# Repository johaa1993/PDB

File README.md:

# PDB

# Kill switch
The goal is to switch high current, voltage with logic level voltage and logic level current.
If somethings goes wrong then the user might want to kill the system until further damages happens.

Mechanical relay or MOSFET can be used for such application.

## MOSFET driver
The MOSFET can be damaged if driven incorectly.

### Drain-source resistance `R_ds`
Applying gate-source voltage will decrease drain-source resistance over time.
If the drain-source resistance decreases too slow while drain-source current is conducted then the MOSFET will heat up and possably get damaged.
The time it takes to reach fully turned on MOSFET depends on gate capacitance, 
gate resistance and the MOSFET gate driver ability to deliver current.

### Gate-source voltage `V_GS`
Applying too high gate-source voltage will damage the MOSFET.

### Parasitic oscillation
The MOSFET internal capacitance and the wires inductance combined will inevitably create a RLC curcuit.
A step response on the `V_GS` will have a oscilation. Higher gate resistance => higher damping, higher switch time. Lower gate resistance => lower damping, lower switch time.
It's up to the user to find a fine balance between the switch time and parasitic oscillation.

http://toshiba.semicon-storage.com/us/design-support/document/application-note.html
Application Precautions: Power MOSFET Application Notes

### More
Taking all these into consideration when designing a MOSFET driver is a hard task.

# Current sensor
The goal is to measure the both high current, low current.

# Fuse
The goal is too protect from short curcuit.

# Power status
The goal is to check if there power on the line.

# Battery cell monitor
The goal is to check if the battery cell is to low.

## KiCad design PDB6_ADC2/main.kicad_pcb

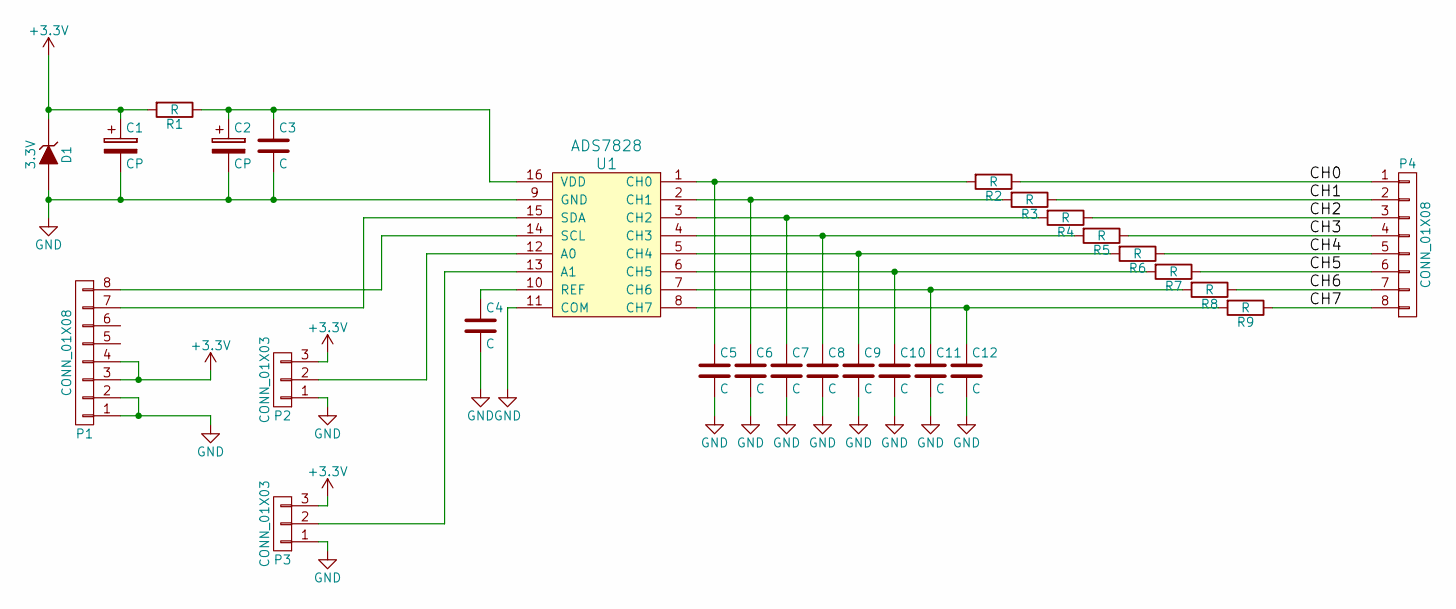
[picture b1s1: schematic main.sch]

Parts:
C1, C2: CP; SMD-1206_Pol
C3, C4, C5, C6, C7, C8, C9, C10, C11, C12: C; C_0805
D1: 3.3V; SOD-123
P1, P4: CONN_01X08; Pin_Header_Straight_1x08_Pitch2.00mm
P2, P3: CONN_01X03; Pad_3
R1, R2, R3, R4, R5, R6, R7, R8, R9: R; R_0805
U1: ADS7828; TSSOP-16_4.4x5mm_Pitch0.65mm

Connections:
+3V3: C1.1, D1.1 (K), P1.3, P1.4, P2.3, P3.3, R1.2
/CH0: P4.1, R2.1
/CH1: P4.2, R3.1
/CH2: P4.3, R4.1
/CH3: P4.4, R5.1
/CH4: P4.5, R6.1
/CH5: P4.6, R7.1
/CH6: P4.7, R8.1
/CH7: P4.8, R9.1
GND: C1.2, C2.2, C3.2, C4.2, C5.2, C6.2, C7.2, C8.2, C9.2, C10.2, C11.2, C12.2, D1.2 (A), P1.1, P1.2, P2.1, P3.1, U1.9 (GND), U1.11 (COM)
unnamed: C2.1, C3.1, R1.1, U1.16 (VDD)
unnamed: C4.1, U1.10 (REF)
unnamed: C5.1, R2.2, U1.1 (CH0)
unnamed: C6.1, R3.2, U1.2 (CH1)
unnamed: C7.1, R4.2, U1.3 (CH2)
unnamed: C8.1, R5.2, U1.4 (CH3)
unnamed: C9.1, R6.2, U1.5 (CH4)
unnamed: C10.1, R7.2, U1.6 (CH5)
unnamed: C11.1, R8.2, U1.7 (CH6)
unnamed: C12.1, R9.2, U1.8 (CH7)
unnamed: P1.7, U1.15 (SDA)
unnamed: P1.8, U1.14 (SCL)
unnamed: P2.2, U1.12 (A0)
unnamed: P3.2, U1.13 (A1)

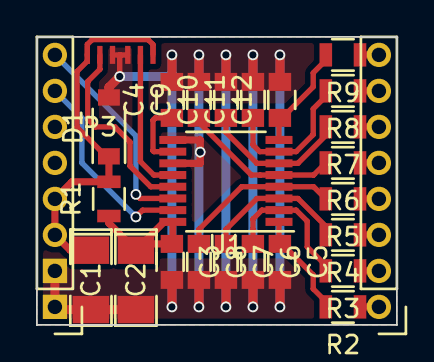
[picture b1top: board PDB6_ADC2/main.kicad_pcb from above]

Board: 2 copper layers, 20.0 x 16.0 mm, 27 parts (0 on the bottom side), 24 nets.

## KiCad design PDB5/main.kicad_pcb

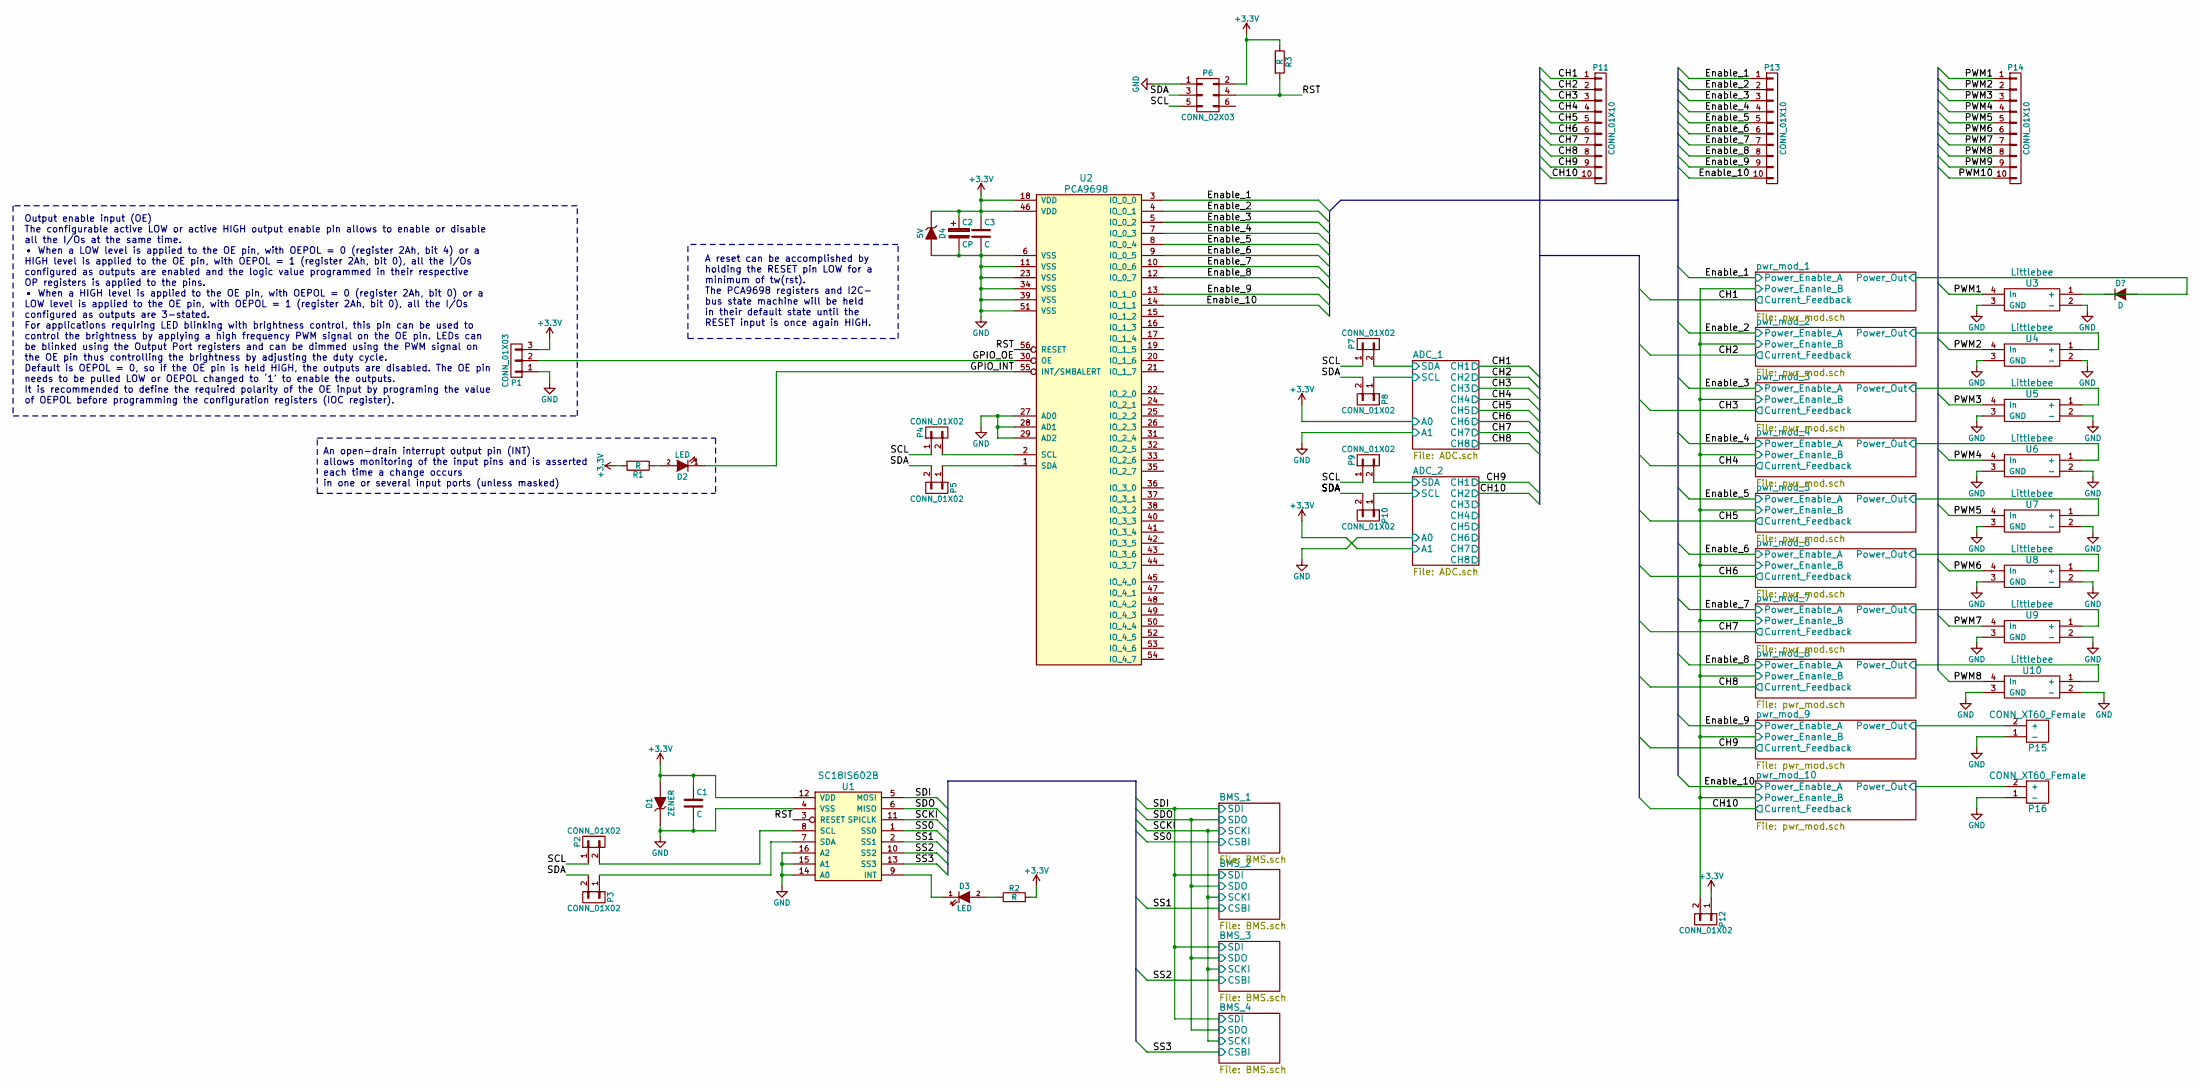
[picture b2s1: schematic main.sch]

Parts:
C1, C3: C; C_0805
C2: CP; SMD-2010_Pol
D1: ZENER; SOD-123
D2, D3: LED; LED_0603
D4: 5V; SOD-123
P1: CONN_01X03; Pin_Header_Straight_1x03
P2, P3, P4, P5, P7, P8, P9, P10, P12: CONN_01X02; Pin_Header_Straight_1x02
P6: CONN_02X03; Pin_Header_Straight_2x03
P11, P13, P14: CONN_01X10; Pin_Header_Straight_1x10
P15, P16: CONN_XT60_Female; XT60
R1, R2: R; R_0603
R3: R
U1: SC18IS602B; TSSOP-16_4.4x5mm_Pitch0.65mm
U2: PCA9698; TSSOP-56_6.1x14mm_Pitch0.5mm
U3, U4, U5, U6, U7, U8, U9, U10: Littlebee

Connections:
+3V3: C1.1, C2.1, C3.1, D1.2 (A), D4.1 (K), P1.3, P6.2, P12.1, R1.2, R2.2, R3.1, U1.12 (VDD), U2.18 (VDD), U2.46 (VDD); also elsewhere on the board
/ADC_1/SCL: P8.1; also elsewhere on the board
/ADC_1/SDA: P7.2; also elsewhere on the board
/ADC_2/SCL: P10.1; also elsewhere on the board
/ADC_2/SDA: P9.2; also elsewhere on the board
/CH1: P11.1; also elsewhere on the board
/CH2: P11.2; also elsewhere on the board
/CH3: P11.3; also elsewhere on the board
/CH4: P11.4; also elsewhere on the board
/CH5: P11.5; also elsewhere on the board
/CH6: P11.6; also elsewhere on the board
/CH7: P11.7; also elsewhere on the board
/CH8: P11.8; also elsewhere on the board
/CH9: P11.9; also elsewhere on the board
/CH10: P11.10; also elsewhere on the board
/Enable_1: P13.1, U2.3 (IO_0_0); also elsewhere on the board
/Enable_2: P13.2, U2.4 (IO_0_1); also elsewhere on the board
/Enable_3: P13.3, U2.5 (IO_0_2); also elsewhere on the board
/Enable_4: P13.4, U2.7 (IO_0_3); also elsewhere on the board
/Enable_5: P13.5, U2.8 (IO_0_4); also elsewhere on the board
/Enable_6: P13.6, U2.9 (IO_0_5); also elsewhere on the board
/Enable_7: P13.7, U2.10 (IO_0_6); also elsewhere on the board
/Enable_8: P13.8, U2.12 (IO_0_7); also elsewhere on the board
/Enable_9: P13.9, U2.13 (IO_1_0); also elsewhere on the board
/Enable_10: P13.10, U2.14 (IO_1_1); also elsewhere on the board
/GPIO_INT: D2.1 (K), U2.55 (INT/SMBALERT)
/GPIO_OE: P1.2, U2.30 (OE)
/PWM1: P14.1, U3.4 (In)
/PWM2: P14.2, U4.4 (In)
/PWM3: P14.3, U5.4 (In)
/PWM4: P14.4, U6.4 (In)
/PWM5: P14.5, U7.4 (In)
/PWM6: P14.6, U8.4 (In)
/PWM7: P14.7, U9.4 (In)
/PWM8: P14.8, U10.4 (In)
/RST: P6.4, R3.2, U1.3 (RESET), U2.56 (RESET)
/SCKI: U1.11 (SPICLK); also elsewhere on the board
/SCL: P2.1, P4.1, P6.5, P7.1, P9.1
/SDA: P3.2, P5.2, P6.3, P8.2, P10.2
/SDI: U1.5 (MOSI); also elsewhere on the board
/SDO: U1.6 (MISO); also elsewhere on the board
/SS0: U1.1 (SS0); also elsewhere on the board
/SS1: U1.2 (SS1); also elsewhere on the board
/SS2: U1.10 (SS2); also elsewhere on the board
/SS3: U1.13 (SS3); also elsewhere on the board
/pwr_mod_1/Power_Enanle_B: P12.2; also elsewhere on the board
/pwr_mod_1/Power_Out: U3.1 (+); also elsewhere on the board
/pwr_mod_2/Power_Out: U4.1 (+); also elsewhere on the board
/pwr_mod_3/Power_Out: U5.1 (+); also elsewhere on the board
/pwr_mod_4/Power_Out: U6.1 (+); also elsewhere on the board
/pwr_mod_5/Power_Out: U7.1 (+); also elsewhere on the board
/pwr_mod_6/Power_Out: U8.1 (+); also elsewhere on the board
/pwr_mod_7/Power_Out: U9.1 (+); also elsewhere on the board
/pwr_mod_8/Power_Out: U10.1 (+); also elsewhere on the board
/pwr_mod_9/Power_Out: P15.2 (+); also elsewhere on the board
/pwr_mod_10/Power_Out: P16.2 (+); also elsewhere on the board
GND: C1.2, C2.2, C3.2, D1.1 (K), D4.2 (A), P1.1, P6.1, P15.1 (-), P16.1 (-), U1.4 (VSS), U1.14 (A0), U1.15 (A1), U1.16 (A2), U2.6 (VSS), U2.11 (VSS), U2.23 (VSS), U2.27 (AD0), U2.28 (AD1), U2.29 (AD2), U2.34 (VSS), U2.39 (VSS), U2.51 (VSS), U3.2 (-), U3.3 (GND), U4.2 (-), U4.3 (GND), U5.2 (-), U5.3 (GND), U6.2 (-), U6.3 (GND), U7.2 (-), U7.3 (GND), U8.2 (-), U8.3 (GND), U9.2 (-), U9.3 (GND), U10.2 (-), U10.3 (GND); also elsewhere on the board
unnamed: D2.2 (A), R1.1
unnamed: D3.1 (K), U1.9 (INT)
unnamed: D3.2 (A), R2.1
unnamed: P2.2, U1.8 (SCL)
unnamed: P3.1, U1.7 (SDA)
unnamed: P4.2, U2.2 (SCL)
unnamed: P5.1, U2.1 (SDA)

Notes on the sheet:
An open-drain interrupt output pin (INT) allows monitoring of the input pins and is asserted each time a change occurs in one or several input ports (unless masked)
Output enable input (OE) The configurable active LOW or active HIGH output enable pin allows to enable or disable all the I/Os at the same time. • When a LOW level is applied to the OE pin, with OEPOL = 0 (register 2Ah, bit 4) or a HIGH level is applied to the OE pin, with OEPOL = 1 (register 2Ah, 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
A reset can be accomplished by holding the RESET pin LOW for a minimum of tw(rst). The PCA9698 registers and I2C- bus state machine will be held in their default state until the RESET input is once again HIGH.

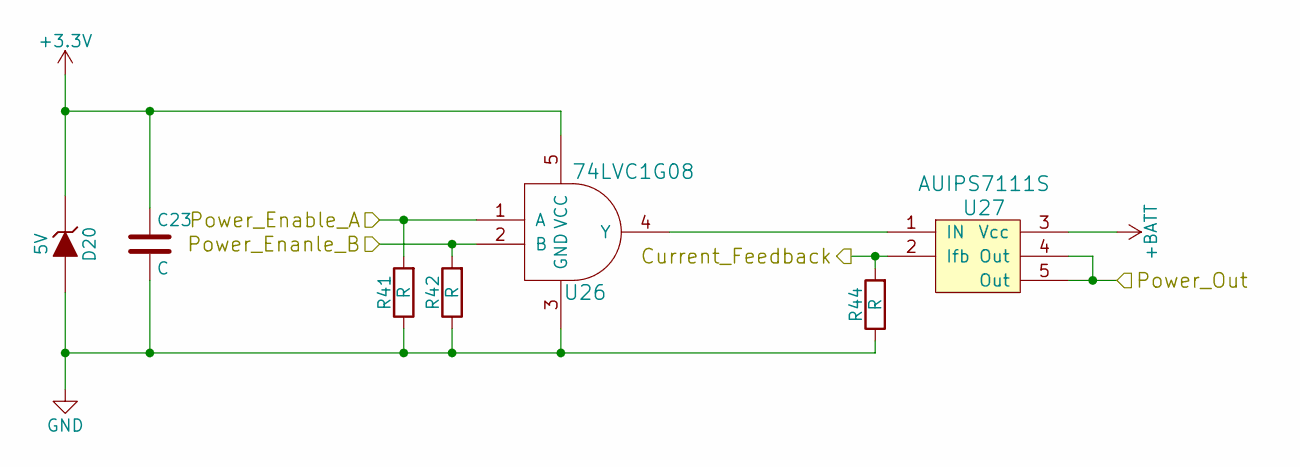
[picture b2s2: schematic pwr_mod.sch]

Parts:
C4: C; C_0805
D5: 5V; SOD-123
R4, R7, R26: R; R_0603
U11: 74LVC1G08; SOT-353
U12: AUIPS7111S; TO-263-!3

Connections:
+3V3: C4.1, D5.1 (K), U11.5 (VCC); also elsewhere on the board
+BATT: U12.3 (Vcc); also elsewhere on the board
/CH1: R7.2, U12.2 (Ifb); also elsewhere on the board
/Enable_1: R4.2, U11.1 (A); also elsewhere on the board
/pwr_mod_1/Power_Enanle_B: R26.2, U11.2 (B); also elsewhere on the board
/pwr_mod_1/Power_Out: U12.4 (Out), U12.5 (Out); also elsewhere on the board
GND: C4.2, D5.2 (A), R4.1, R7.1, R26.1, U11.3 (GND); also elsewhere on the board
unnamed: U11.4 (Y), U12.1 (IN)

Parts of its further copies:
C5, C18, C19, C20, C21, C22, C23, C24, C25: C; C_0805
D7, D10, D12, D14, D16, D18, D20, D22, D24: 5V; SOD-123
R5, R8, R9, R11, R21, R22, R24, R25, R28, R29, R30, R32, R33, R34, R36, R37, R38, R40, R41, R42, R44, R45, R46, R48, R49, R50, R52: R; R_0603
U13, U16, U18, U20, U22, U24, U26, U28, U30: 74LVC1G08; SOT-353
U14, U17, U19, U21, U23, U25, U27, U29, U31: AUIPS7111S; TO-263-!3

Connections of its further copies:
+3V3: C5.1, C18.1, C19.1, C20.1, C21.1, C22.1, C23.1, C24.1, C25.1, D7.1 (K), D10.1 (K), D12.1 (K), D14.1 (K), D16.1 (K), D18.1 (K), D20.1 (K), D22.1 (K), D24.1 (K), U13.5 (VCC), U16.5 (VCC), U18.5 (VCC), U20.5 (VCC), U22.5 (VCC), U24.5 (VCC), U26.5 (VCC), U28.5 (VCC), U30.5 (VCC); also elsewhere on the board
+BATT: U14.3 (Vcc), U17.3 (Vcc), U19.3 (Vcc), U21.3 (Vcc), U23.3 (Vcc), U25.3 (Vcc), U27.3 (Vcc), U29.3 (Vcc), U31.3 (Vcc); also elsewhere on the board
/CH2: R11.2, U14.2 (Ifb); also elsewhere on the board
/CH3: R24.2, U17.2 (Ifb); also elsewhere on the board
/CH4: R28.2, U19.2 (Ifb); also elsewhere on the board
/CH5: R32.2, U21.2 (Ifb); also elsewhere on the board
/CH6: R36.2, U23.2 (Ifb); also elsewhere on the board
/CH7: R40.2, U25.2 (Ifb); also elsewhere on the board
/CH8: R44.2, U27.2 (Ifb); also elsewhere on the board
/CH9: R48.2, U29.2 (Ifb); also elsewhere on the board
/CH10: R52.2, U31.2 (Ifb); also elsewhere on the board
/Enable_2: R8.2, U13.1 (A); also elsewhere on the board
/Enable_3: R21.2, U16.1 (A); also elsewhere on the board
/Enable_4: R25.2, U18.1 (A); also elsewhere on the board
/Enable_5: R29.2, U20.1 (A); also elsewhere on the board
/Enable_6: R33.2, U22.1 (A); also elsewhere on the board
/Enable_7: R37.2, U24.1 (A); also elsewhere on the board
/Enable_8: R41.2, U26.1 (A); also elsewhere on the board
/Enable_9: R45.2, U28.1 (A); also elsewhere on the board
/Enable_10: R49.2, U30.1 (A); also elsewhere on the board
/pwr_mod_1/Power_Enanle_B: R5.2, R9.2, R22.2, R30.2, R34.2, R38.2, R42.2, R46.2, R50.2, U13.2 (B), U16.2 (B), U18.2 (B), U20.2 (B), U22.2 (B), U24.2 (B), U26.2 (B), U28.2 (B), U30.2 (B); also elsewhere on the board
/pwr_mod_2/Power_Out: U14.4 (Out), U14.5 (Out); also elsewhere on the board
/pwr_mod_3/Power_Out: U17.4 (Out), U17.5 (Out); also elsewhere on the board
/pwr_mod_4/Power_Out: U19.4 (Out), U19.5 (Out); also elsewhere on the board
/pwr_mod_5/Power_Out: U21.4 (Out), U21.5 (Out); also elsewhere on the board
/pwr_mod_6/Power_Out: U23.4 (Out), U23.5 (Out); also elsewhere on the board
/pwr_mod_7/Power_Out: U25.4 (Out), U25.5 (Out); also elsewhere on the board
/pwr_mod_8/Power_Out: U27.4 (Out), U27.5 (Out); also elsewhere on the board
/pwr_mod_9/Power_Out: U29.4 (Out), U29.5 (Out); also elsewhere on the board
/pwr_mod_10/Power_Out: U31.4 (Out), U31.5 (Out); also elsewhere on the board
GND: C5.2, C18.2, C19.2, C20.2, C21.2, C22.2, C23.2, C24.2, C25.2, D7.2 (A), D10.2 (A), D12.2 (A), D14.2 (A), D16.2 (A), D18.2 (A), D20.2 (A), D22.2 (A), D24.2 (A), R5.1, R8.1, R9.1, R11.1, R21.1, R22.1, R24.1, R25.1, R28.1, R29.1, R30.1, R32.1, R33.1, R34.1, R36.1, R37.1, R38.1, R40.1, R41.1, R42.1, R44.1, R45.1, R46.1, R48.1, R49.1, R50.1, R52.1, U13.3 (GND), U16.3 (GND), U18.3 (GND), U20.3 (GND), U22.3 (GND), U24.3 (GND), U26.3 (GND), U28.3 (GND), U30.3 (GND); also elsewhere on the board
unnamed: U13.4 (Y), U14.1 (IN)
unnamed: U16.4 (Y), U17.1 (IN)
unnamed: U18.4 (Y), U19.1 (IN)
unnamed: U20.4 (Y), U21.1 (IN)
unnamed: U22.4 (Y), U23.1 (IN)
unnamed: U24.4 (Y), U25.1 (IN)
unnamed: U26.4 (Y), U27.1 (IN)
unnamed: U28.4 (Y), U29.1 (IN)
unnamed: U30.4 (Y), U31.1 (IN)

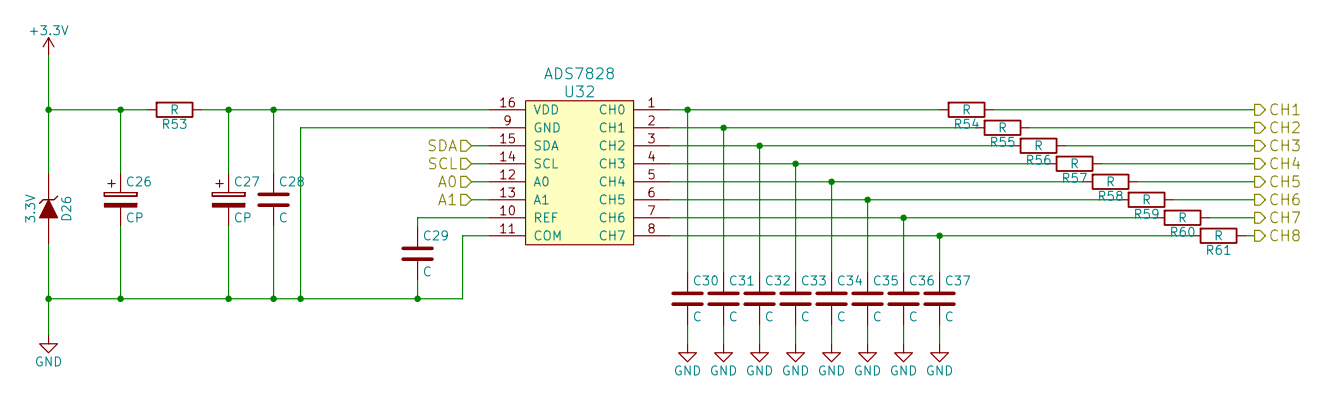
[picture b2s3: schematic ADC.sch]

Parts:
C6, C7: CP; SMD-2010_Pol
C8, C9, C10, C11, C12, C13, C14, C15, C16, C17: C; C_0805
D9: 3.3V; SOD-123
R12, R13, R14, R15, R16, R17, R18, R19, R20: R; R_0603
U15: ADS7828; TSSOP-16_4.4x5mm_Pitch0.65mm

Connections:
+3V3: C6.1, D9.1 (K), R12.2, U15.12 (A0); also elsewhere on the board
/ADC_1/SCL: U15.14 (SCL); also elsewhere on the board
/ADC_1/SDA: U15.15 (SDA); also elsewhere on the board
/CH1: R13.1; also elsewhere on the board
/CH2: R14.1; also elsewhere on the board
/CH3: R15.1; also elsewhere on the board
/CH4: R16.1; also elsewhere on the board
/CH5: R17.1; also elsewhere on the board
/CH6: R18.1; also elsewhere on the board
/CH7: R19.1; also elsewhere on the board
/CH8: R20.1; also elsewhere on the board
GND: C6.2, C7.2, C8.2, C9.2, C10.2, C11.2, C12.2, C13.2, C14.2, C15.2, C16.2, C17.2, D9.2 (A), U15.9 (GND), U15.11 (COM), U15.13 (A1); also elsewhere on the board
unnamed: C7.1, C8.1, R12.1, U15.16 (VDD)
unnamed: C9.1, U15.10 (REF)
unnamed: C10.1, R13.2, U15.1 (CH0)
unnamed: C11.1, R14.2, U15.2 (CH1)
unnamed: C12.1, R15.2, U15.3 (CH2)
unnamed: C13.1, R16.2, U15.4 (CH3)
unnamed: C14.1, R17.2, U15.5 (CH4)
unnamed: C15.1, R18.2, U15.6 (CH5)
unnamed: C16.1, R19.2, U15.7 (CH6)
unnamed: C17.1, R20.2, U15.8 (CH7)

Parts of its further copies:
C26, C27: CP; SMD-2010_Pol
C28, C29, C30, C31, C32, C33, C34, C35, C36, C37: C; C_0805
D26: 3.3V; SOD-123
R53, R54, R55, R56, R57, R58, R59, R60, R61: R; R_0603
U32: ADS7828; TSSOP-16_4.4x5mm_Pitch0.65mm

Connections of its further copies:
+3V3: C26.1, D26.1 (K), R53.2, U32.13 (A1); also elsewhere on the board
/ADC_2/SCL: U32.14 (SCL); also elsewhere on the board
/ADC_2/SDA: U32.15 (SDA); also elsewhere on the board
/CH9: R54.1; also elsewhere on the board
/CH10: R55.1; also elsewhere on the board
GND: C26.2, C27.2, C28.2, C29.2, C30.2, C31.2, C32.2, C33.2, C34.2, C35.2, C36.2, C37.2, D26.2 (A), U32.9 (GND), U32.11 (COM), U32.12 (A0); also elsewhere on the board
unnamed: C27.1, C28.1, R53.1, U32.16 (VDD)
unnamed: C29.1, U32.10 (REF)
unnamed: C30.1, R54.2, U32.1 (CH0)
unnamed: C31.1, R55.2, U32.2 (CH1)
unnamed: C32.1, R56.2, U32.3 (CH2)
unnamed: C33.1, R57.2, U32.4 (CH3)
unnamed: C34.1, R58.2, U32.5 (CH4)
unnamed: C35.1, R59.2, U32.6 (CH5)
unnamed: C36.1, R60.2, U32.7 (CH6)
unnamed: C37.1, R61.2, U32.8 (CH7)

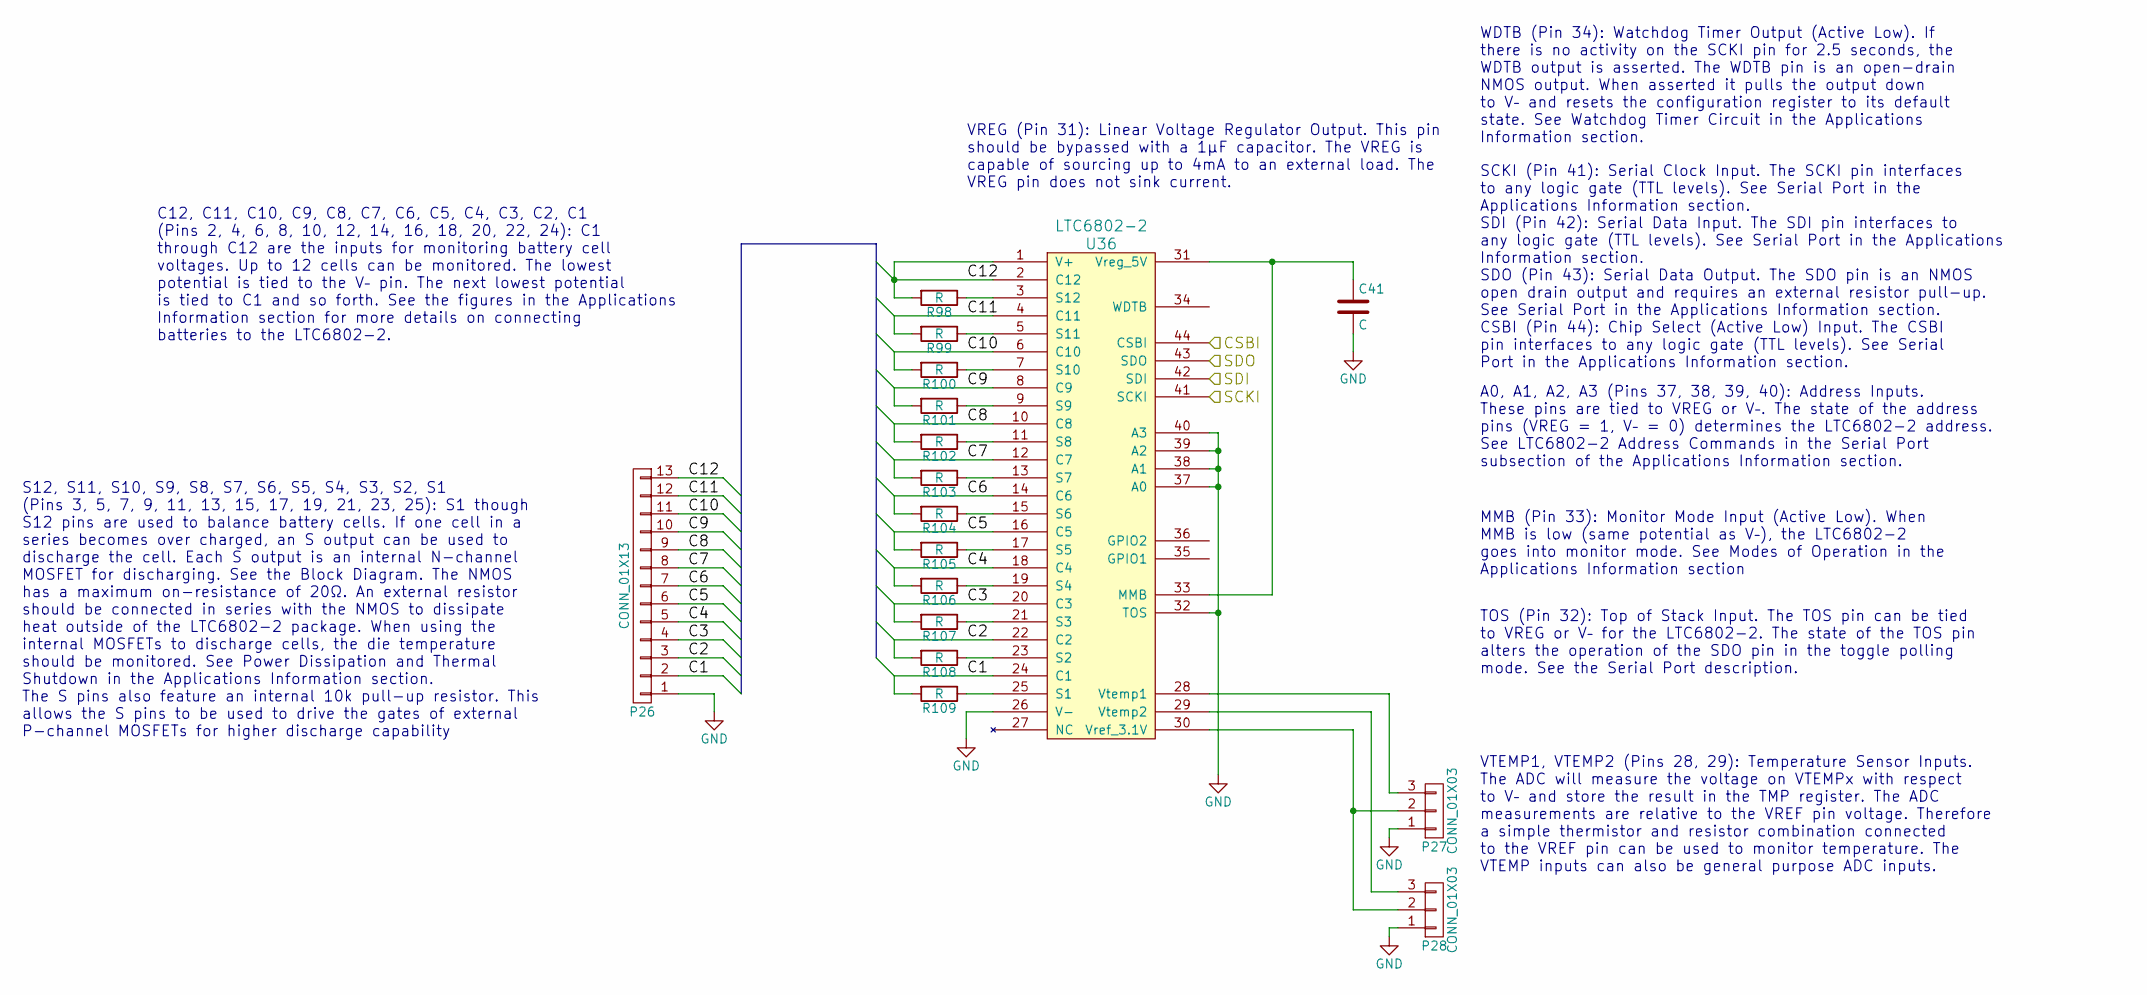
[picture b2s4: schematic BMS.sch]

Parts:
C38: C; C_0805
P17: CONN_01X13; Pin_Header_Straight_1x13
P18, P19: CONN_01X03; Pin_Header_Straight_1x03
R62, R63, R64, R65, R66, R67, R68, R69, R70, R71, R72, R73: R; R_0805
U33: LTC6802-2; SSOP-44

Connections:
/BMS_1/C1: P17.2, R73.2, U33.24 (C1)
/BMS_1/C2: P17.3, R72.2, U33.22 (C2)
/BMS_1/C3: P17.4, R71.2, U33.20 (C3)
/BMS_1/C4: P17.5, R70.2, U33.18 (C4)
/BMS_1/C5: P17.6, R69.2, U33.16 (C5)
/BMS_1/C6: P17.7, R68.2, U33.14 (C6)
/BMS_1/C7: P17.8, R67.2, U33.12 (C7)
/BMS_1/C8: P17.9, R66.2, U33.10 (C8)
/BMS_1/C9: P17.10, R65.2, U33.8 (C9)
/BMS_1/C10: P17.11, R64.2, U33.6 (C10)
/BMS_1/C11: P17.12, R63.2, U33.4 (C11)
/BMS_1/C12: P17.13, R62.2, U33.1 (V+), U33.2 (C12)
/SCKI: U33.41 (SCKI); also elsewhere on the board
/SDI: U33.42 (SDI); also elsewhere on the board
/SDO: U33.43 (SDO); also elsewhere on the board
/SS0: U33.44 (CSBI); also elsewhere on the board
GND: C38.2, P17.1, P18.1, P19.1, U33.26 (V-), U33.32 (TOS), U33.37 (A0), U33.38 (A1), U33.39 (A2), U33.40 (A3); also elsewhere on the board
unnamed: C38.1, U33.31 (Vreg_5V), U33.33 (MMB)
unnamed: P18.2, P19.2, U33.30 (Vref_3.1V)
unnamed: P18.3, U33.28 (Vtemp1)
unnamed: P19.3, U33.29 (Vtemp2)
unnamed: R62.1, U33.3 (S12)
unnamed: R63.1, U33.5 (S11)
unnamed: R64.1, U33.7 (S10)
unnamed: R65.1, U33.9 (S9)
unnamed: R66.1, U33.11 (S8)
unnamed: R67.1, U33.13 (S7)
unnamed: R68.1, U33.15 (S6)
unnamed: R69.1, U33.17 (S5)
unnamed: R70.1, U33.19 (S4)
unnamed: R71.1, U33.21 (S3)
unnamed: R72.1, U33.23 (S2)
unnamed: R73.1, U33.25 (S1)

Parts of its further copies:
C39, C40, C41: C; C_0805
P20, P23, P26: CONN_01X13; Pin_Header_Straight_1x13
P21, P22, P24, P25, P27, P28: CONN_01X03; Pin_Header_Straight_1x03
R74, R75, R76, R77, R78, R79, R80, R81, R82, R83, R84, R85, R86, R87, R88, R89, R90, R91, R92, R93, R94, R95, R96, R97, R98, R99, R100, R101, R102, R103, R104, R105, R106, R107, R108, R109: R; R_0805
U34, U35, U36: LTC6802-2; SSOP-44

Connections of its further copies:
/BMS_2/C1: P20.2, R85.2, U34.24 (C1)
/BMS_2/C2: P20.3, R84.2, U34.22 (C2)
/BMS_2/C3: P20.4, R83.2, U34.20 (C3)
/BMS_2/C4: P20.5, R82.2, U34.18 (C4)
/BMS_2/C5: P20.6, R81.2, U34.16 (C5)
/BMS_2/C6: P20.7, R80.2, U34.14 (C6)
/BMS_2/C7: P20.8, R79.2, U34.12 (C7)
/BMS_2/C8: P20.9, R78.2, U34.10 (C8)
/BMS_2/C9: P20.10, R77.2, U34.8 (C9)
/BMS_2/C10: P20.11, R76.2, U34.6 (C10)
/BMS_2/C11: P20.12, R75.2, U34.4 (C11)
/BMS_2/C12: P20.13, R74.2, U34.1 (V+), U34.2 (C12)
/BMS_3/C1: P23.2, R97.2, U35.24 (C1)
/BMS_3/C2: P23.3, R96.2, U35.22 (C2)
/BMS_3/C3: P23.4, R95.2, U35.20 (C3)
/BMS_3/C4: P23.5, R94.2, U35.18 (C4)
/BMS_3/C5: P23.6, R93.2, U35.16 (C5)
/BMS_3/C6: P23.7, R92.2, U35.14 (C6)
/BMS_3/C7: P23.8, R91.2, U35.12 (C7)
/BMS_3/C8: P23.9, R90.2, U35.10 (C8)
/BMS_3/C9: P23.10, R89.2, U35.8 (C9)
/BMS_3/C10: P23.11, R88.2, U35.6 (C10)
/BMS_3/C11: P23.12, R87.2, U35.4 (C11)
/BMS_3/C12: P23.13, R86.2, U35.1 (V+), U35.2 (C12)
/BMS_4/C1: P26.2, R109.2, U36.24 (C1)
/BMS_4/C2: P26.3, R108.2, U36.22 (C2)
/BMS_4/C3: P26.4, R107.2, U36.20 (C3)
/BMS_4/C4: P26.5, R106.2, U36.18 (C4)
/BMS_4/C5: P26.6, R105.2, U36.16 (C5)
/BMS_4/C6: P26.7, R104.2, U36.14 (C6)
/BMS_4/C7: P26.8, R103.2, U36.12 (C7)
/BMS_4/C8: P26.9, R102.2, U36.10 (C8)
/BMS_4/C9: P26.10, R101.2, U36.8 (C9)
/BMS_4/C10: P26.11, R100.2, U36.6 (C10)
/BMS_4/C11: P26.12, R99.2, U36.4 (C11)
/BMS_4/C12: P26.13, R98.2, U36.1 (V+), U36.2 (C12)
/SCKI: U34.41 (SCKI), U35.41 (SCKI), U36.41 (SCKI); also elsewhere on the board
/SDI: U34.42 (SDI), U35.42 (SDI), U36.42 (SDI); also elsewhere on the board
/SDO: U34.43 (SDO), U35.43 (SDO), U36.43 (SDO); also elsewhere on the board
/SS1: U34.44 (CSBI); also elsewhere on the board
/SS2: U35.44 (CSBI); also elsewhere on the board
/SS3: U36.44 (CSBI); also elsewhere on the board
GND: C39.2, C40.2, C41.2, P20.1, P21.1, P22.1, P23.1, P24.1, P25.1, P26.1, P27.1, P28.1, U34.26 (V-), U34.32 (TOS), U34.37 (A0), U34.38 (A1), U34.39 (A2), U34.40 (A3), U35.26 (V-), U35.32 (TOS), U35.37 (A0), U35.38 (A1), U35.39 (A2), U35.40 (A3), U36.26 (V-), U36.32 (TOS), U36.37 (A0), U36.38 (A1), U36.39 (A2), U36.40 (A3); also elsewhere on the board
unnamed: C39.1, U34.31 (Vreg_5V), U34.33 (MMB)
unnamed: C40.1, U35.31 (Vreg_5V), U35.33 (MMB)
unnamed: C41.1, U36.31 (Vreg_5V), U36.33 (MMB)
unnamed: P21.2, P22.2, U34.30 (Vref_3.1V)
unnamed: P21.3, U34.28 (Vtemp1)
unnamed: P22.3, U34.29 (Vtemp2)
unnamed: P24.2, P25.2, U35.30 (Vref_3.1V)
unnamed: P24.3, U35.28 (Vtemp1)
unnamed: P25.3, U35.29 (Vtemp2)
unnamed: P27.2, P28.2, U36.30 (Vref_3.1V)
unnamed: P27.3, U36.28 (Vtemp1)
unnamed: P28.3, U36.29 (Vtemp2)
unnamed: R74.1, U34.3 (S12)
unnamed: R75.1, U34.5 (S11)
unnamed: R76.1, U34.7 (S10)
unnamed: R77.1, U34.9 (S9)
unnamed: R78.1, U34.11 (S8)
unnamed: R79.1, U34.13 (S7)
unnamed: R80.1, U34.15 (S6)
unnamed: R81.1, U34.17 (S5)
unnamed: R82.1, U34.19 (S4)
unnamed: R83.1, U34.21 (S3)
unnamed: R84.1, U34.23 (S2)
unnamed: R85.1, U34.25 (S1)
unnamed: R86.1, U35.3 (S12)
unnamed: R87.1, U35.5 (S11)
unnamed: R88.1, U35.7 (S10)
unnamed: R89.1, U35.9 (S9)
unnamed: R90.1, U35.11 (S8)
unnamed: R91.1, U35.13 (S7)
unnamed: R92.1, U35.15 (S6)
unnamed: R93.1, U35.17 (S5)
unnamed: R94.1, U35.19 (S4)
unnamed: R95.1, U35.21 (S3)
unnamed: R96.1, U35.23 (S2)
unnamed: R97.1, U35.25 (S1)
unnamed: R98.1, U36.3 (S12)
unnamed: R99.1, U36.5 (S11)
unnamed: R100.1, U36.7 (S10)
unnamed: R101.1, U36.9 (S9)
unnamed: R102.1, U36.11 (S8)
unnamed: R103.1, U36.13 (S7)
unnamed: R104.1, U36.15 (S6)
unnamed: R105.1, U36.17 (S5)
unnamed: R106.1, U36.19 (S4)
unnamed: R107.1, U36.21 (S3)
unnamed: R108.1, U36.23 (S2)
unnamed: R109.1, U36.25 (S1)

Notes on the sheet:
WDTB (Pin 34): Watchdog Timer Output (Active Low). If there is no activity on the SCKI pin for 2.5 seconds, the WDTB output is asserted. The WDTB pin is an open-drain NMOS output. When asserted it pulls the output down to V– and resets the configuration register to its default state. See Watchdog T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
VTEMP1, VTEMP2 (Pins 28, 29): Temperature Sensor Inputs. The ADC will measure the voltage on VTEMPx with respect to V– and store the result in the TMP register. The ADC measurements are relative to the VREF pin voltage. Therefore a simple thermistor and resistor combination connected to the VREF pi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
SCKI (Pin 41): Serial Clock Input. The SCKI pin interfaces to any logic gate (TTL levels). See Serial Port in the Applications Information section. SDI (Pin 42): Serial Data Input. The SDI pin interfaces to any logic gate (TTL levels). See Serial Port in the Applications Information section. SDO (P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
C12, C11, C10, C9, C8, C7, C6, C5, C4, C3, C2, C1 (Pins 2, 4, 6, 8, 10, 12, 14, 16, 18, 20, 22, 24): C1 through C12 are the inputs for monitoring battery cell voltages. Up to 12 cells can be monitored. The lowest potential is tied to the V– pin. The next lowest potential is tied to C1 and so forth.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
S12, S11, S10, S9, S8, S7, S6, S5, S4, S3, S2, S1 (Pins 3, 5, 7, 9, 11, 13, 15, 17, 19, 21, 23, 25): S1 though S12 pins are used to balance battery cells. If one cell in a series becomes over charged, an S output can be used to discharge the cell. Each S output is an internal N-channel MOSFET for d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
MMB (Pin 33): Monitor Mode Input (Active Low). When MMB is low (same potential as V–), the LTC6802-2 goes into monitor mode. See Modes of Operation in the Applications Information section
TOS (Pin 32): Top of Stack Input. The TOS pin can be tied to VREG or V– for the LTC6802-2. The state of the TOS pin alters the operation of the SDO pin in the toggle polling mode. See the Serial Port description.
A0, A1, A2, A3 (Pins 37, 38, 39, 40): Address Inputs. These pins are tied to VREG or V–. The state of the address pins (VREG = 1, V– = 0) determines the LTC6802-2 address. See LTC6802-2 Address Commands in the Serial Port subsection of the Applications Information section.
VREG (Pin 31): Linear Voltage Regulator Output. This pin should be bypassed with a 1µF capacitor. The VREG is capable of sourcing up to 4mA to an external load. The VREG pin does not sink current.

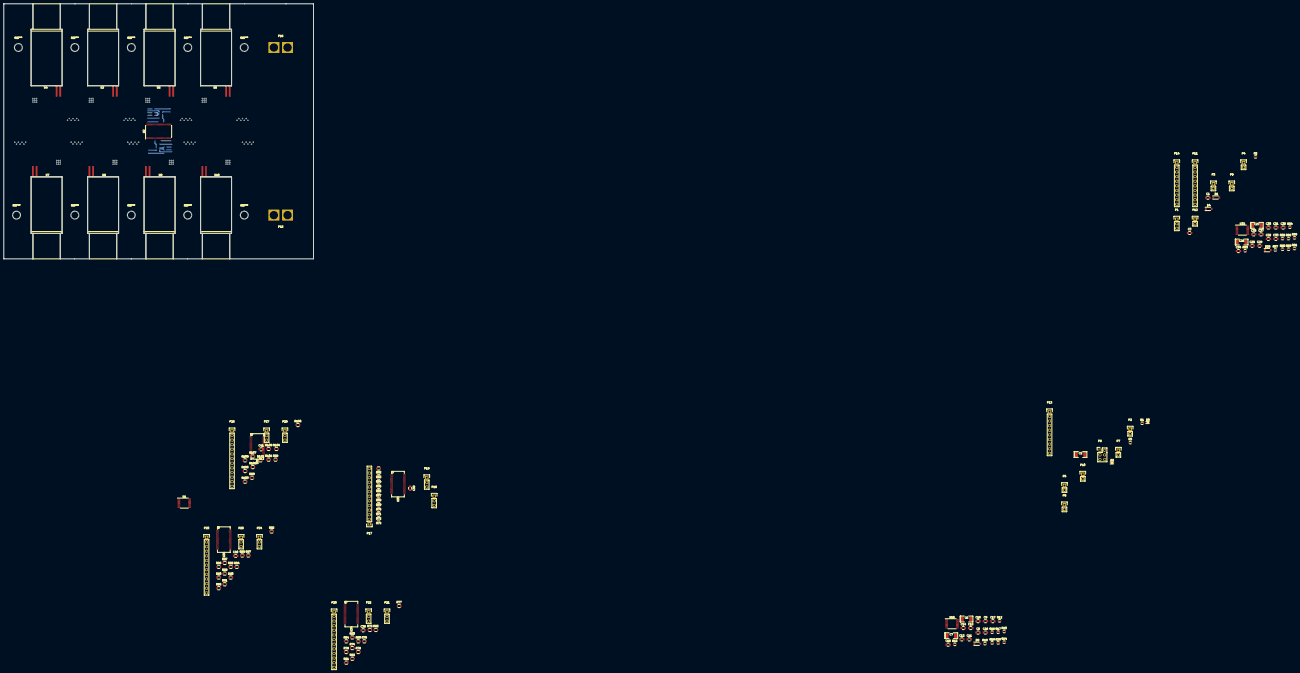
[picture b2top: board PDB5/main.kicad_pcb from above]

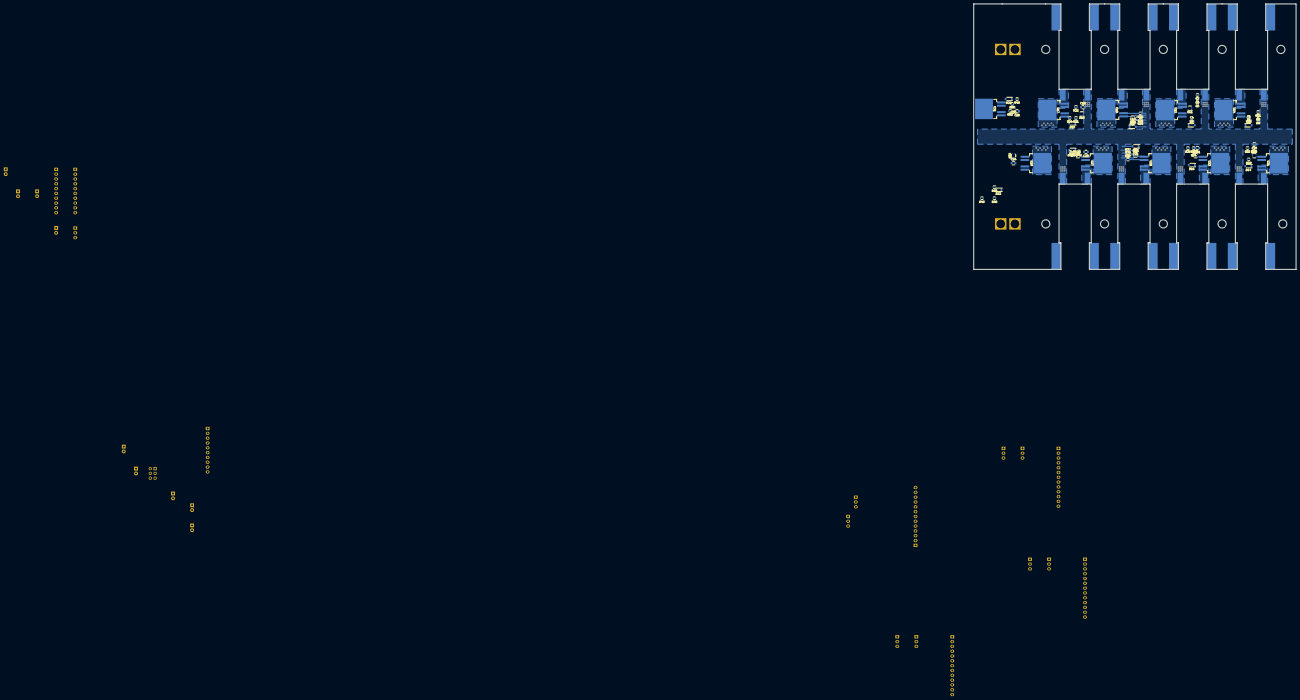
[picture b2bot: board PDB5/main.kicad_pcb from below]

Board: 4 copper layers, 170.0 x 140.0 mm, 220 parts (70 on the bottom side), 207 nets.

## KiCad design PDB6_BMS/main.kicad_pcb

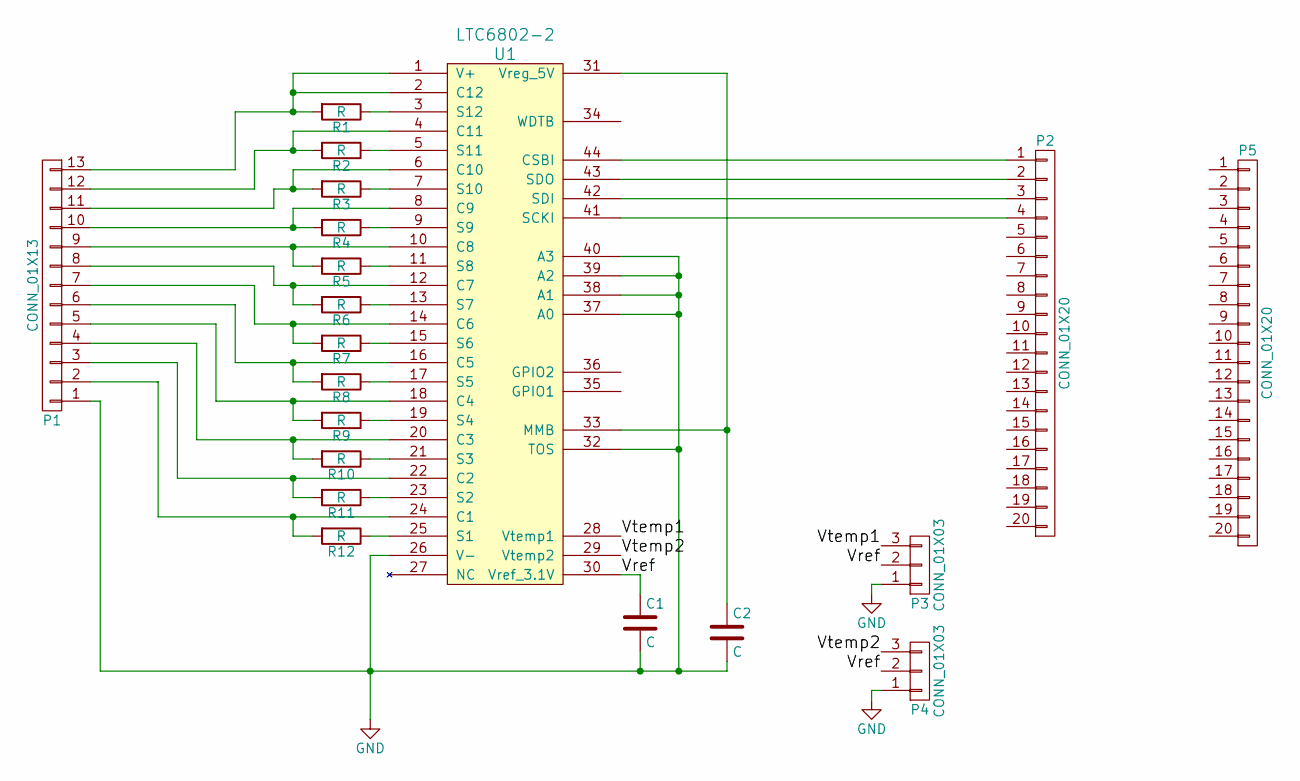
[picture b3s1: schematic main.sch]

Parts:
C1, C2: C; C_0805
P1: CONN_01X13; Pin_Header_Straight_1x13
P2, P5: CONN_01X20; Pin_Header_Straight_1x20_Pitch2.00mm
P3, P4: CONN_01X03; Pin_Header_Straight_1x03
R1, R2, R3, R4, R5, R6, R7, R8, R9, R10, R11, R12: R; R_0805
U1: LTC6802-2; SSOP-44

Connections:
/Vref: C1.1, P3.2, P4.2, U1.30 (Vref_3.1V)
/Vtemp1: P3.3, U1.28 (Vtemp1)
/Vtemp2: P4.3, U1.29 (Vtemp2)
GND: C1.2, C2.2, P1.1, P3.1, P4.1, U1.26 (V-), U1.32 (TOS), U1.37 (A0), U1.38 (A1), U1.39 (A2), U1.40 (A3)
unnamed: C2.1, U1.31 (Vreg_5V), U1.33 (MMB)
unnamed: P1.2, R12.2, U1.24 (C1)
unnamed: P1.3, R11.2, U1.22 (C2)
unnamed: P1.4, R10.2, U1.20 (C3)
unnamed: P1.5, R9.2, U1.18 (C4)
unnamed: P1.6, R8.2, U1.16 (C5)
unnamed: P1.7, R7.2, U1.14 (C6)
unnamed: P1.8, R6.2, U1.12 (C7)
unnamed: P1.9, R5.2, U1.10 (C8)
unnamed: P1.10, R4.2, U1.8 (C9)
unnamed: P1.11, R3.2, U1.6 (C10)
unnamed: P1.12, R2.2, U1.4 (C11)
unnamed: P1.13, R1.2, U1.1 (V+), U1.2 (C12)
unnamed: P2.1, U1.44 (CSBI)
unnamed: P2.2, U1.43 (SDO)
unnamed: P2.3, U1.42 (SDI)
unnamed: P2.4, U1.41 (SCKI)
unnamed: R1.1, U1.3 (S12)
unnamed: R2.1, U1.5 (S11)
unnamed: R3.1, U1.7 (S10)
unnamed: R4.1, U1.9 (S9)
unnamed: R5.1, U1.11 (S8)
unnamed: R6.1, U1.13 (S7)
unnamed: R7.1, U1.15 (S6)
unnamed: R8.1, U1.17 (S5)
unnamed: R9.1, U1.19 (S4)
unnamed: R10.1, U1.21 (S3)
unnamed: R11.1, U1.23 (S2)
unnamed: R12.1, U1.25 (S1)
